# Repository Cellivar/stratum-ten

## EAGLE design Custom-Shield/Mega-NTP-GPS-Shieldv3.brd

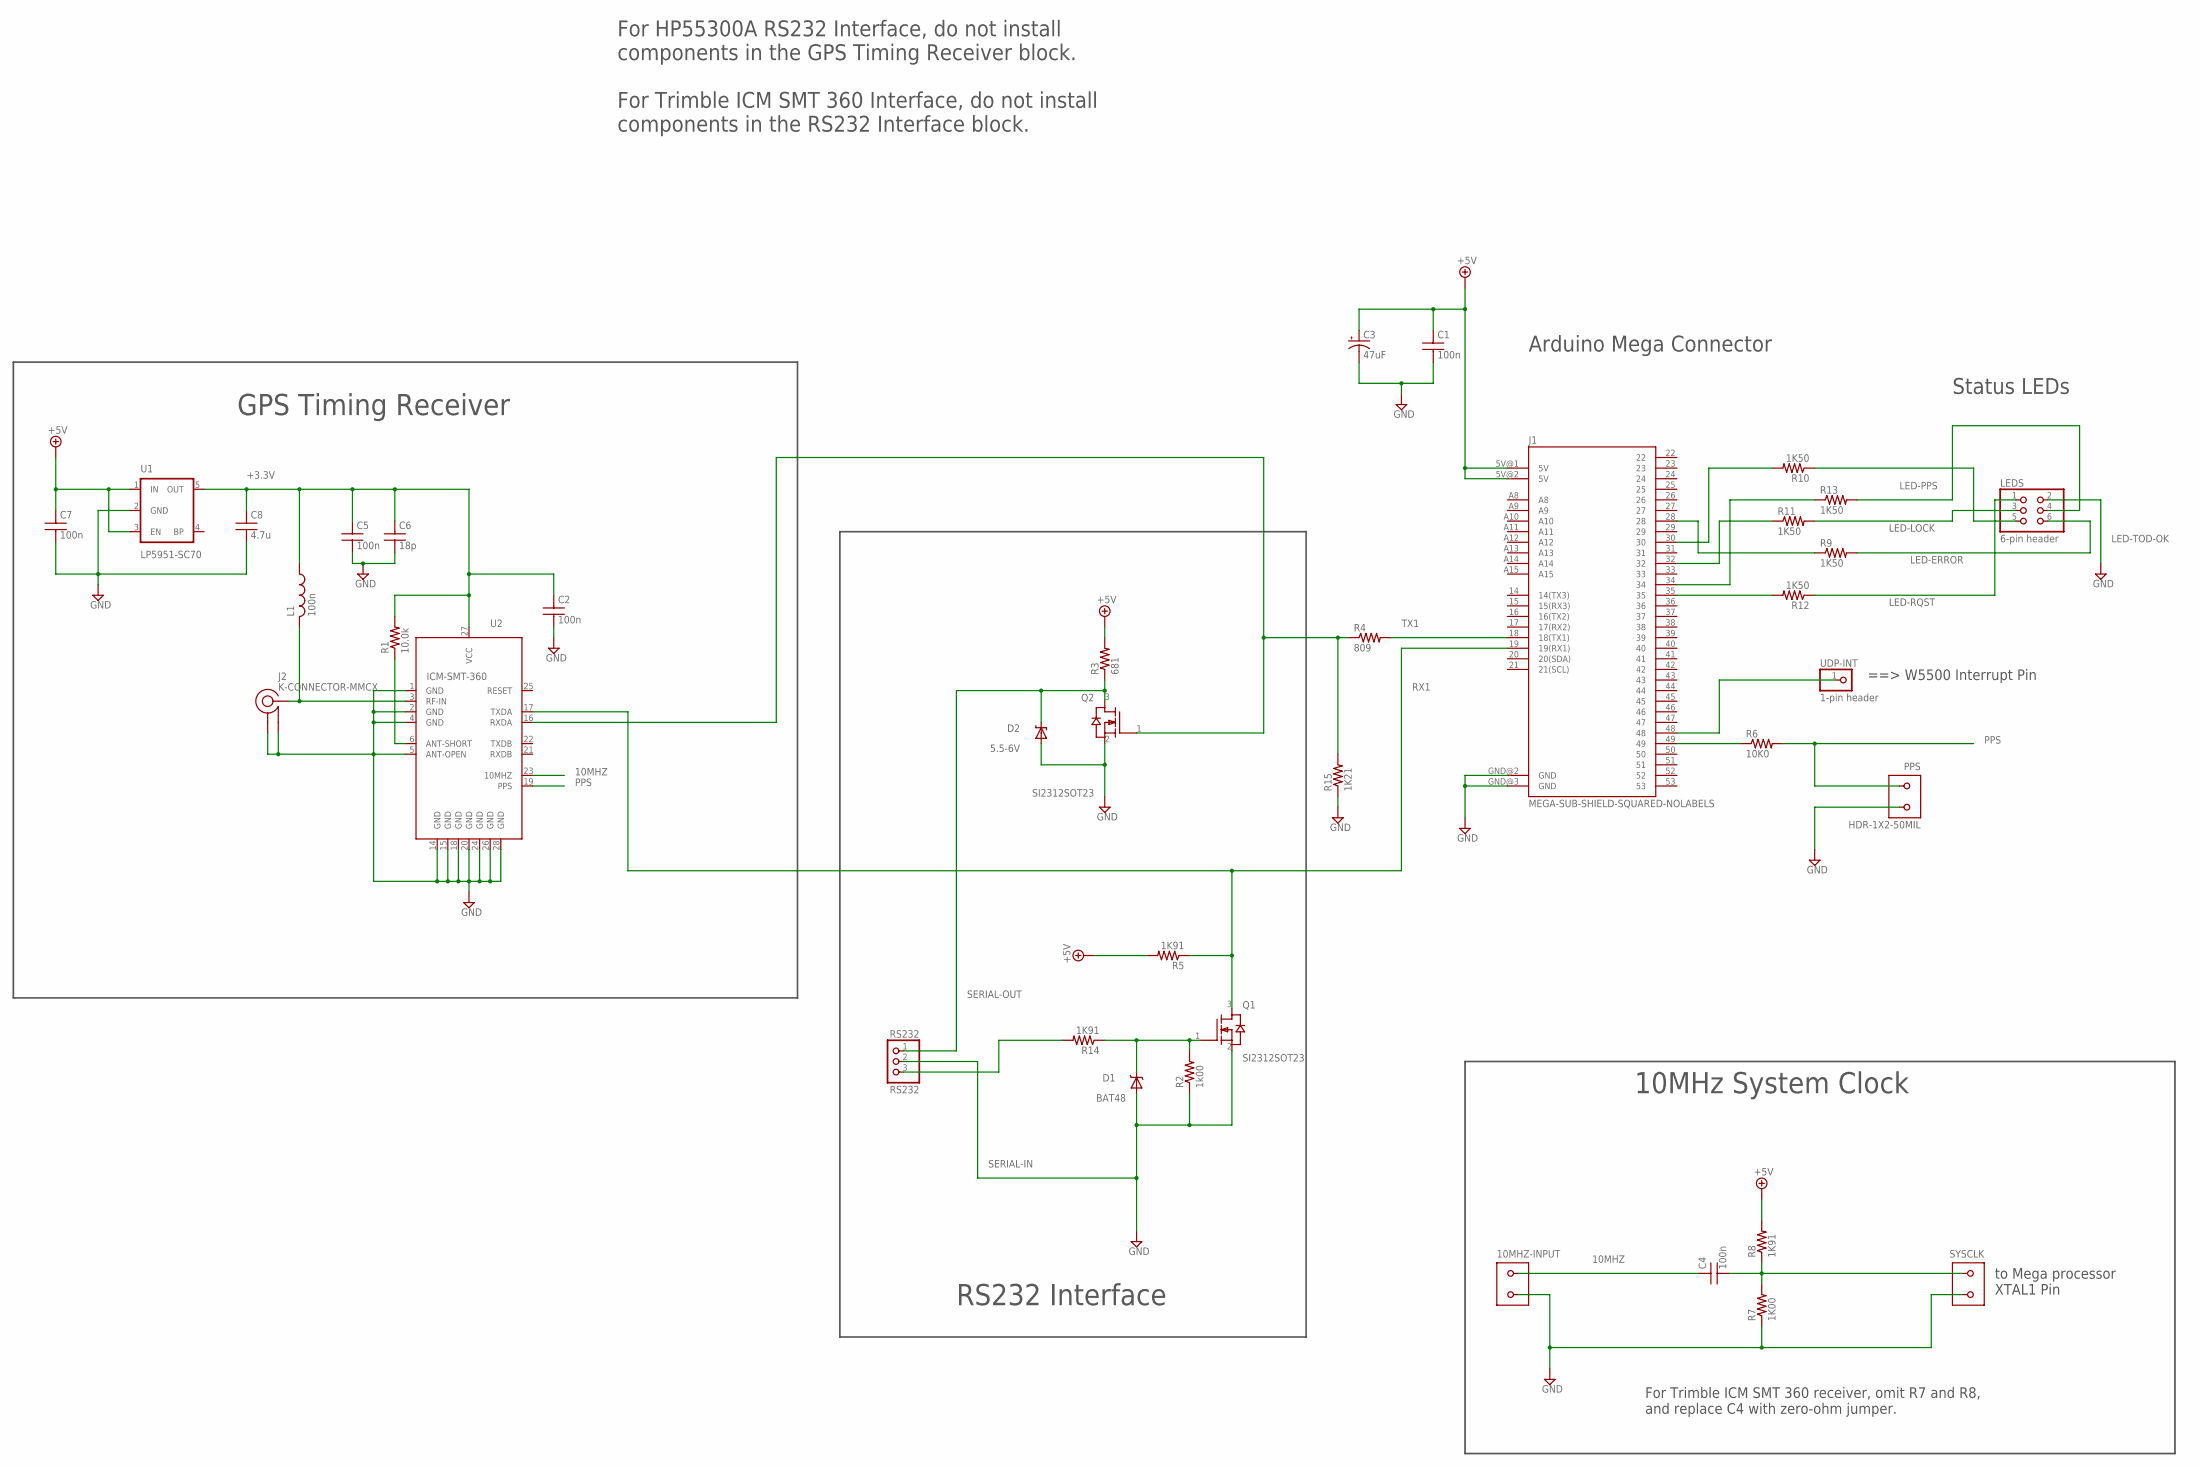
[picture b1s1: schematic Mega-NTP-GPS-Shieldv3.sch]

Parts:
10MHZ-INPUT: HDR-1X2-100MIL; 1X02-100MIL
C1: 100n; AVX-0805; MPN 0805(3/5)C104(J/K)ATxx
C2: 100n; AVX-0805-NT; MPN 0805(3/5)C104(J/K)ATxx
C3: 47uF; EIA3528; MPN TR3B476K010C0350
C4: 100n; AVX-0603; MPN 0603(3/5)C104(J/K)ATxx
C5, C7: 100n; AVX-0603-NT; MPN 0603(3/5)C104(J/K)ATxx
C6: 18p; AVX-0402-NT; MPN 04025A180JATxx
C8: 4.7u; AVX-0805-NT; MPN C0805YC475KATxx
D1: BAT48; SOD-323
D2: 5.5-6V; SOD-323
J1: MEGA-SUB-SHIELD-SQUARED-NOLABELS
J2: K-CONNECTOR-MMCX; MOLEX-MMCX-VERTICAL; MPN 73415-206x; DIGIKEY WM3914CT-ND
L1: 100n; AVX-0603-NT; MPN LQW18ANR10J00
LEDS: 6-pin header; 2X03-50MIL
PPS: HDR-1X2-50MIL; 1X02-50MIL
Q1, Q2: SI2312SOT23; SOT23; MPN SI2312BDS
R1: 10.0k; AVX-0603; MPN CRCW060310.0kFKxx
R2: 1k00; AVX-0603-NT; MPN CRCW06034K02FKxx
R3: 681; AVX-0603; MPN CRCW0603DNP (681)FKxx
R4: 809; AVX-0603; MPN CRCW06031K91FKxx
R5, R8: 1K91; AVX-0603; MPN CRCW06031K91FKxx
R6: 10K0; AVX-0603; MPN CRCW060310K0FKxx
R7: 1K00; AVX-0603; MPN CRCW06031K91FKxx
R9, R10, R11, R12, R13: 1K50; AVX-0603; MPN CRCW06031K50FKxx
R14: 1K91; AVX-0603; MPN CRCW06034K02FKxx
R15: 1K21; AVX-0603-NT; MPN CRCW06034K02FKxx
RS232: RS232; 1X03-100MIL
SYSCLK: HDR-1X2-100MIL; 1X02-100MIL
U1: LP5951-SC70; SC70; MPN LP5951MG-3.3/NOPB
U2: ICM-SMT-360; TRIMBLE-ICM-SMT-360; MPN ICM-SMT-360
UDP-INT: 1-pin header; 1X01

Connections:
10MHZ: 10MHZ-INPUT.1, C4.1, U2.23 (10MHZ)
+3.3V: C2.1, C5.1, C6.1, C8.1, L1.1, R1.2, U1.5 (OUT), U2.27 (VCC)
+5V: C1.1, C3.A (+), C7.1, J1.5V@1 (5V), J1.5V@2 (5V), R3.2, R5.2, R8.2, U1.1 (IN), U1.3 (EN)
ANTENNA: J2.CENTER (1), L1.2, U2.3 (RF-IN)
GND: 10MHZ-INPUT.2, C1.2, C2.2, C3.C (-), C5.2, C6.2, C7.2, C8.2, D1.2 (A), D2.2 (A), J1.GND@2 (GND), J1.GND@3 (GND), J2.GND1, J2.GND2, LEDS.2, PPS.2, Q1.2 (S), Q2.2 (S), R2.1, R7.1, R15.1, RS232.2, SYSCLK.2, U1.2 (GND), U2.1 (GND), U2.2 (GND), U2.4 (GND), U2.5 (ANT-OPEN), U2.14 (GND), U2.15 (GND), U2.18 (GND), U2.20 (GND), U2.24 (GND), U2.26 (GND), U2.28 (GND)
LED-ERROR: LEDS.6, R9.2
LED-LOCK: LEDS.3, R11.2
LED-PPS: LEDS.4, R13.2
LED-RQST: LEDS.1, R12.1
LED-TOD-OK: LEDS.5, R10.1
unnamed: Q2.1 (G), R4.1, R15.2, U2.16 (RXDA)
unnamed: C4.2, R7.2, R8.1, SYSCLK.1
unnamed: R1.1, U2.6 (ANT-SHORT)
unnamed: J1.49, R6.1
unnamed: D1.1 (C), Q1.1 (G), R2.2, R14.1
unnamed: J1.48, UDP-INT.1
unnamed: J1.34, R13.1
unnamed: J1.35, R12.2
unnamed: J1.32, R11.1
unnamed: J1.30, R10.2
unnamed: J1.28, R9.1
PPS: PPS.1, R6.2, U2.19 (PPS)
RX1: J1.19 (19(RX1)), Q1.3 (D), R5.1, U2.17 (TXDA)
SERIAL-IN: R14.2, RS232.3
SERIAL-OUT: D2.1 (C), Q2.3 (D), R3.1, RS232.1
TX1: J1.18 (18(TX1)), R4.2

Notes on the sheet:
10MHz System Clock
RS232 Interface
Status LEDs
==> W5500 Interrupt Pin
to Mega processor XTAL1 Pin
GPS Timing Receiver
Arduino Mega Connector
For HP55300A RS232 Interface, do not install components in the GPS Timing Receiver block. For Trimble ICM SMT 360 Interface, do not install components in the RS232 Interface block.
For Trimble ICM SMT 360 receiver, omit R7 and R8, and replace C4 with zero-ohm jumper.

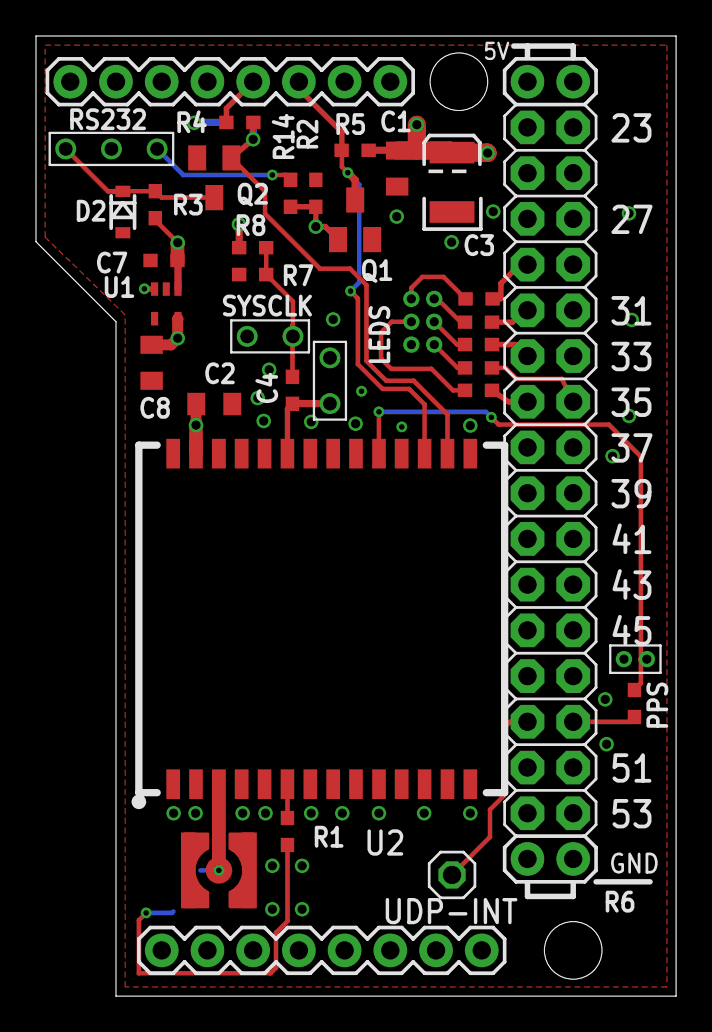
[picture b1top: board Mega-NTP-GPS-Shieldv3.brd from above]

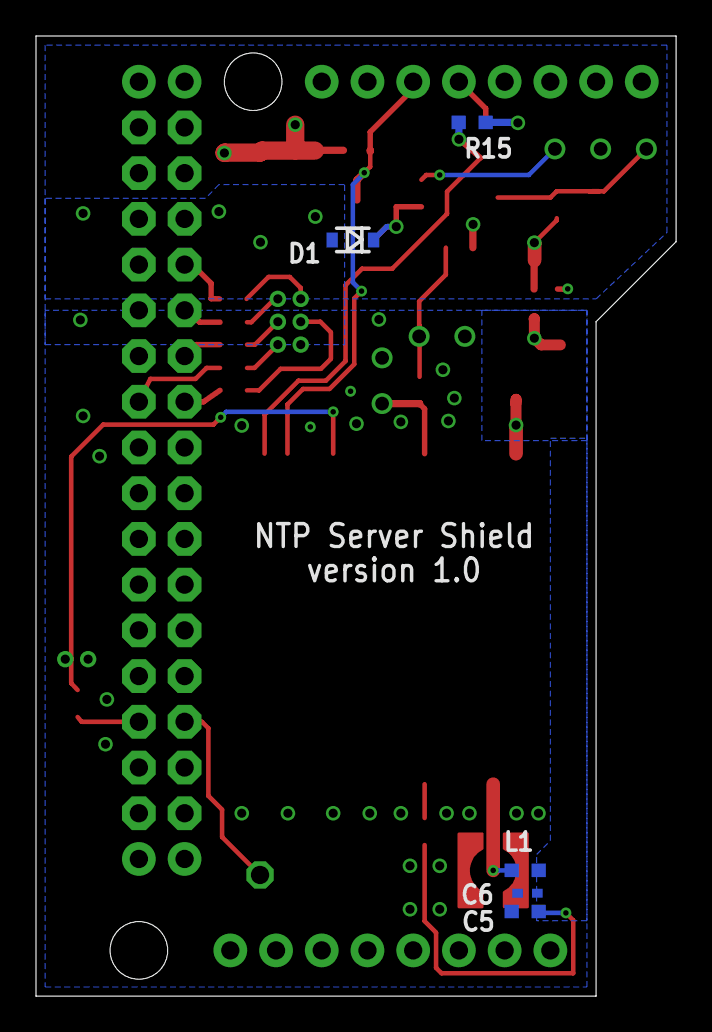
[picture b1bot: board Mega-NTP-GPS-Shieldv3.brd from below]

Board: 2 copper layers, 35.6 x 53.3 mm, 38 parts (5 on the bottom side), 26 nets.

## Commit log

2021-02-14 Initial dump of content

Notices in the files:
parts and their libraries:
SparkFun-Capacitors: Licensing: CC v3.0 Share-Alike You are welcome to use this library for commercial purposes.
